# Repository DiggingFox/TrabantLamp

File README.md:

# TrabantLamp
Světélko ze zadního světla trabanta  
Ovládání zařízení lze vypozorovat z následujícího videa: https://www.youtube.com/shorts/cp-2GQ39OJE

# Struktura
- HW
  - CNC
    - tištěné spoje vznikaly na CNC fréze
    - zde naleznete podpůrné soubory
  - KiCAD
    - projekt celého zařízení se schématem a plošnými spoji
- Pictures
  - obrázky
- SW
  - firmware pro STM8 (ST Visual Develop)
  - ve složce Debug je nejdůležitější .s19 a .elf soubor, které se nahrají do procesoru

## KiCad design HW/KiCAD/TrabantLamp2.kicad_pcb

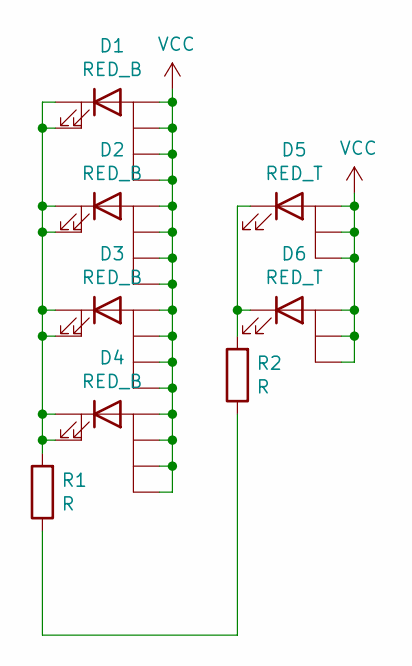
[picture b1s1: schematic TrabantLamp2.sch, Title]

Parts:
D1, D2, D3, D4: RED_B; LED_3232_6Pin
D5, D6: RED_T; LED_3528
R1, R2: R; R_1206_3216Metric_Pad1.42x1.75mm_HandSolder

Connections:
unnamed: D1.2 (K), D1.5 (K), D2.2 (K), D2.5 (K), D3.2 (K), D3.5 (K), D4.2 (K), D4.5 (K), R1.2
unnamed: D5.1 (K), D6.1 (K), R2.2
unnamed: R1.1, R2.1
VCC: D1.1 (A), D1.3 (A), D1.4 (A), D1.6 (A), D2.1 (A), D2.3 (A), D2.4 (A), D2.6 (A), D3.1 (A), D3.3 (A), D3.4 (A), D3.6 (A), D4.1 (A), D4.3 (A), D4.4 (A), D4.6 (A), D5.2 (A), D5.3 (A), D5.4 (A), D6.2 (A), D6.3 (A), D6.4 (A)

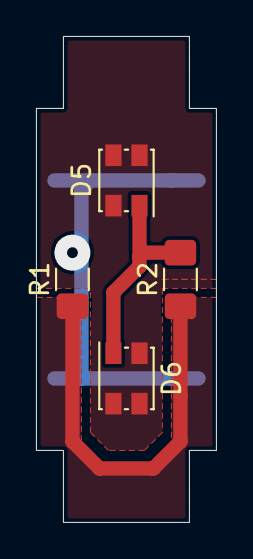
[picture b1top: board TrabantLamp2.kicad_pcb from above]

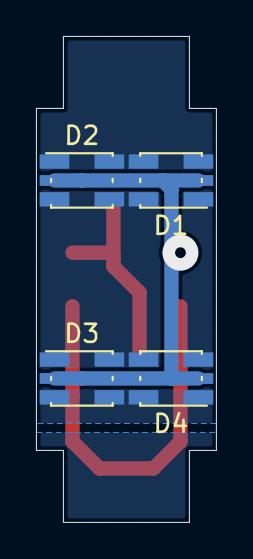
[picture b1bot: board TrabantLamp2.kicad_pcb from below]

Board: 2 copper layers, 10.0 x 27.0 mm, 8 parts (4 on the bottom side), 4 nets.

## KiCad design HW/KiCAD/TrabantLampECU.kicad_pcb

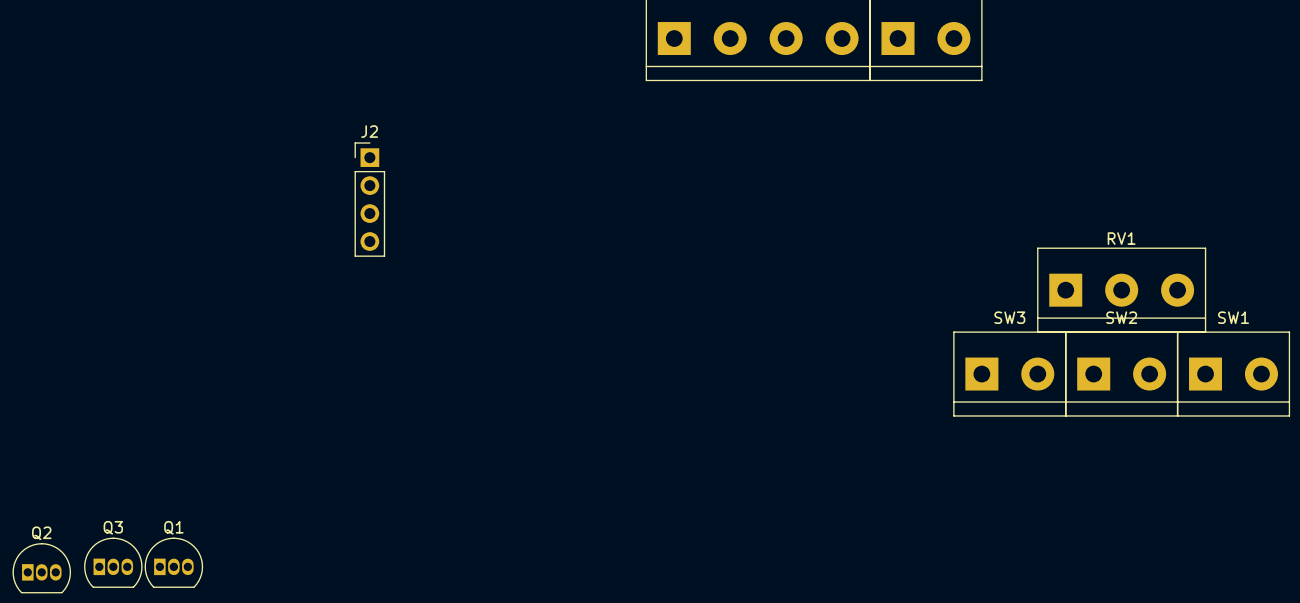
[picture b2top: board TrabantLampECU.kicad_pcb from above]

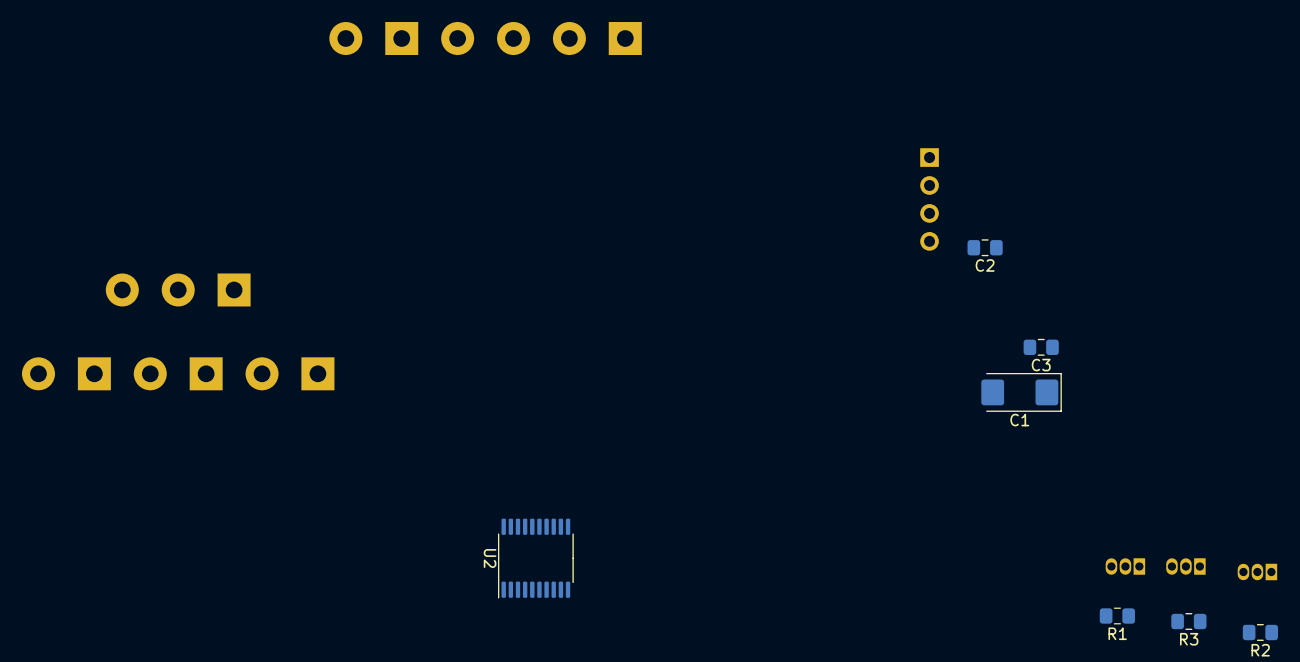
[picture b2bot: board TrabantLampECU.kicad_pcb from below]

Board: 2 copper layers, 17 parts (7 on the bottom side), 19 nets, no tracks yet.

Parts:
C1: CP; CP_EIA-6032-28_Kemet-C
C2, C3: C; C_0805_2012Metric_Pad1.15x1.40mm_HandSolder
J1: Power_Supply; TerminalBlock_bornier-2_P5.08mm
J2: Conn_SWIM; PinHeader_1x04_P2.54mm_Vertical
J3: Conn_LEDs; TerminalBlock_bornier-4_P5.08mm
Q1, Q2, Q3: 2N3904; TO-92_Inline
R1, R2, R3: 1k; R_0805_2012Metric_Pad1.15x1.40mm_HandSolder
RV1: R_POT; TerminalBlock_bornier-3_P5.08mm
SW1: SW_LED_R1; TerminalBlock_bornier-2_P5.08mm
SW2: SW_LED_R2; TerminalBlock_bornier-2_P5.08mm
SW3: SW_LED_O; TerminalBlock_bornier-2_P5.08mm
U2: STM8S003F3P; TSSOP-20_4.4x6.5mm_P0.65mm

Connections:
+3V3: J2.3, U2.9
+5V: C1.1, C2.1, J1.2, J3.1, RV1.1
/LED_O: J3.4, Q3.3
/LED_R1: J3.2, Q1.3
/LED_R2: J3.3, Q2.3
/NRST: J2.2, U2.4
/PIN_LED_O: R3.2, U2.17
/PIN_LED_R1: R1.2, U2.13
/PIN_LED_R2: R2.2, U2.16
/PIN_POT: RV1.2, U2.20
/SWIM: J2.1, U2.18
/SW_LED_O: SW3.1, U2.3
/SW_LED_R1: SW1.1, U2.1
/SW_LED_R2: SW2.1, U2.2
GND: C1.2, C2.2, C3.2, J1.1, J2.4, Q1.1, Q2.1, Q3.1, RV1.3, SW1.2, SW2.2, SW3.2, U2.7
unnamed: C3.1, U2.8
unnamed: Q1.2, R1.1
unnamed: Q2.2, R2.1
unnamed: Q3.2, R3.1

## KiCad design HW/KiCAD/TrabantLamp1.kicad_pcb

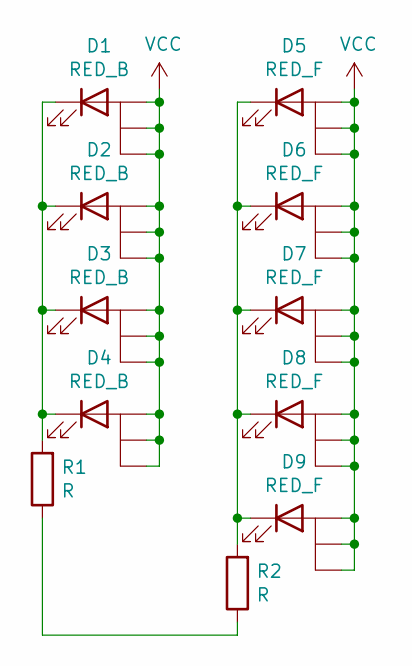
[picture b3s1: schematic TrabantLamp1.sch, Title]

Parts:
D1, D2, D3, D4: RED_B; LED_Kingbright_AAA3528ESGCT
D5, D6, D7, D8, D9: RED_F; LED_Kingbright_AAA3528ESGCT
R1, R2: R; R_1206_3216Metric_Pad1.42x1.75mm_HandSolder

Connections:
unnamed: D1.1 (K), D2.1 (K), D3.1 (K), D4.1 (K), R1.2
unnamed: D5.1 (K), D6.1 (K), D7.1 (K), D8.1 (K), D9.1 (K), R2.2
unnamed: R1.1, R2.1
VCC: D1.2 (A), D1.3 (A), D1.4 (A), D2.2 (A), D2.3 (A), D2.4 (A), D3.2 (A), D3.3 (A), D3.4 (A), D4.2 (A), D4.3 (A), D4.4 (A), D5.2 (A), D5.3 (A), D5.4 (A), D6.2 (A), D6.3 (A), D6.4 (A), D7.2 (A), D7.3 (A), D7.4 (A), D8.2 (A), D8.3 (A), D8.4 (A), D9.2 (A), D9.3 (A), D9.4 (A)

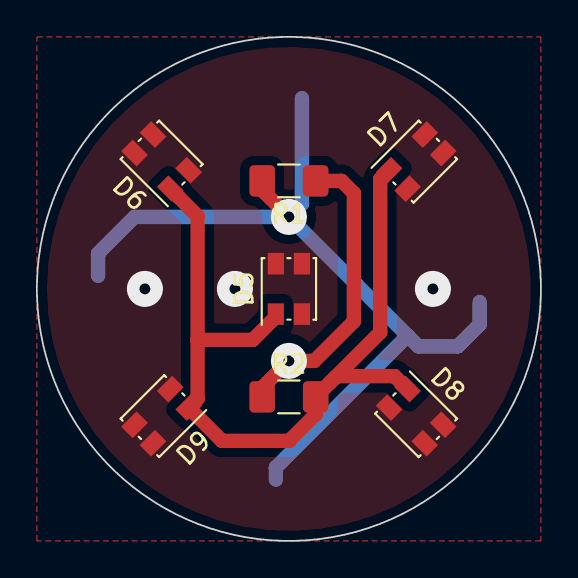
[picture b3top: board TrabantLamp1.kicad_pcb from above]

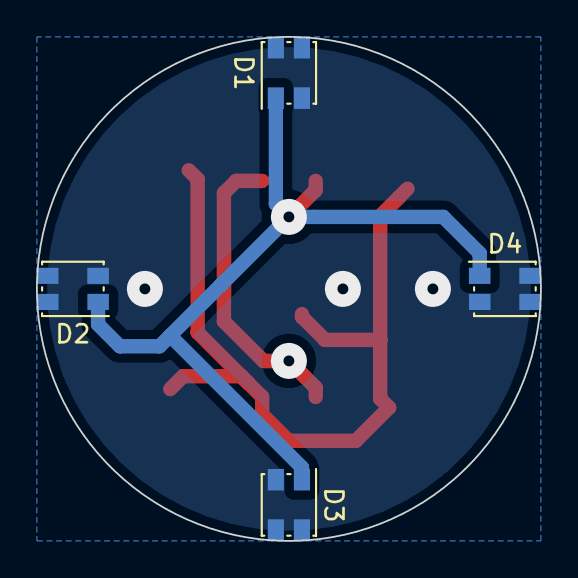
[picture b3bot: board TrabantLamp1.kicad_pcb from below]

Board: 2 copper layers, 28.0 x 28.0 mm, 11 parts (4 on the bottom side), 4 nets.

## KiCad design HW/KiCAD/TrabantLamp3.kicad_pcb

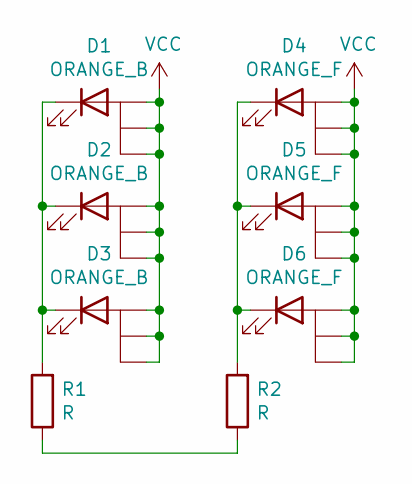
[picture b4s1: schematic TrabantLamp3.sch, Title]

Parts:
D1, D2, D3: ORANGE_B; LED_3528
D4, D5, D6: ORANGE_F; LED_3528
R1, R2: R; R_1206_3216Metric_Pad1.42x1.75mm_HandSolder

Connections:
unnamed: D1.1 (K), D2.1 (K), D3.1 (K), R1.2
unnamed: D4.1 (K), D5.1 (K), D6.1 (K), R2.2
unnamed: R1.1, R2.1
VCC: D1.2 (A), D1.3 (A), D1.4 (A), D2.2 (A), D2.3 (A), D2.4 (A), D3.2 (A), D3.3 (A), D3.4 (A), D4.2 (A), D4.3 (A), D4.4 (A), D5.2 (A), D5.3 (A), D5.4 (A), D6.2 (A), D6.3 (A), D6.4 (A)

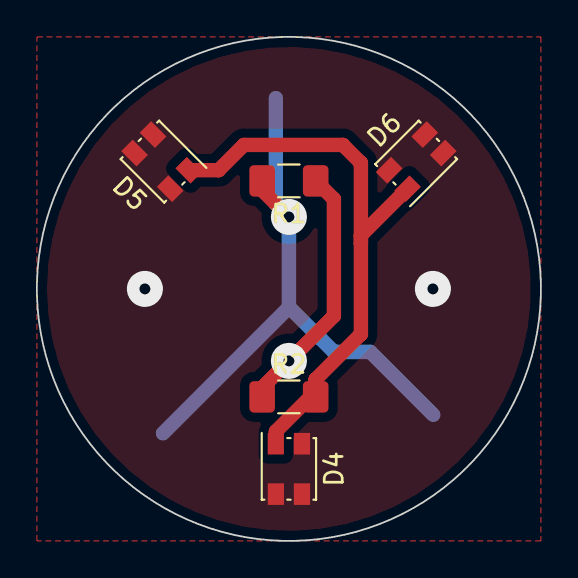
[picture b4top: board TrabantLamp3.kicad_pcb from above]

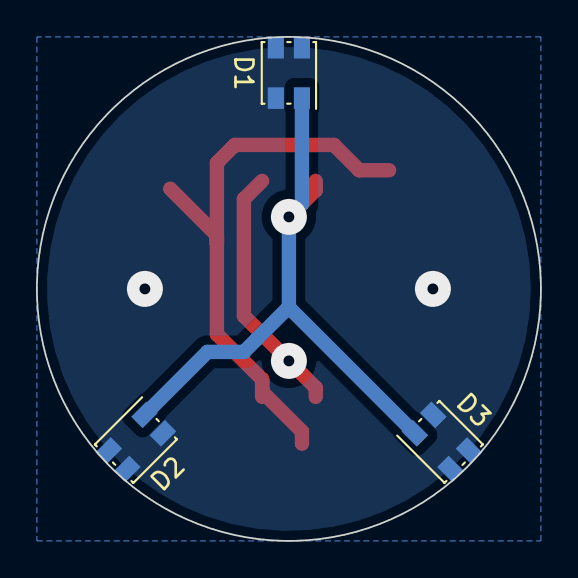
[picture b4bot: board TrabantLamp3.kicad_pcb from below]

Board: 2 copper layers, 28.0 x 28.0 mm, 8 parts (3 on the bottom side), 4 nets.

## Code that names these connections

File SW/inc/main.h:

#define GPIO_LED GPIOC

#define PIN_LED_R1 3	// TIM1_CH3
#define PIN_LED_O 6		// TIM1_CH1
#define PIN_LED_R2 7	// TIM1_CH2

#define GPIO_SW GPIOD

#define PIN_SW_R 6
#define PIN_SW_O 5

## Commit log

2023-10-30 Initial push of all files
2023-10-30 adde few more pictures
